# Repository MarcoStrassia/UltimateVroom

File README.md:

# UltimateVroom

UltimateVroom is a dual-motor brushless controller for a Boosted Board V1. Marco and I are building it to replace the dead stock ESC.

It runs from a 12S A123 26650 pack, which is 39.6 V nominal and 43.2 V charged, and drives two motors. An STM32F103 does the control, IRS2104 gate drivers switch CSD19532 FETs, and the board is 4 layers.

The KiCad project is in `MotorController-Rebuild/`. GitHub doesn't render KiCad files, so clone the repo and open `MotorController-Rebuild/MotorController-Rebuild.kicad_pro` in KiCad 10. `MotorController-Rebuild/docs/` has our spec PDF, design notes, and notes and photos of the stock ESC. `MotorController-Rebuild/review/current/previews/` has images of the board and a PDF of the schematic. `earlier-schematic/` is Marco's first schematic.

The board is routed. ERC has 0 errors and 7 warnings (four-way junctions). DRC has 0 errors and 0 unconnected items, and the schematic matches the board.

Still open: motor current limits, a thermal check, firmware, the Bluetooth remote, and fitting the board into the Boosted V1 ESC footprint, which is about 84 x 100 mm with six phase pads.

Patrick Liu and Marco Strassia, UCSB

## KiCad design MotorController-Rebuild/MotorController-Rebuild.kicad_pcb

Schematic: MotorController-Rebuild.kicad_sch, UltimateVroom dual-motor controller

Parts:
C1, C4: 0.1uF; C_0603_1608Metric; MPN C0603C104K5RACTU
C2, C3, C5: 0.1uF; C_0805_2012Metric; MPN C0805C104K5RACTU
C10, C15, C20, C44, C65, C70, C75, C84, C85: 1uF 50V; C_0805_2012Metric; MPN C0805C105K5RACTU
C11, C16, C21, C43, C66, C71, C76: 4.7uF 25V; C_0805_2012Metric; MPN C0805C475K3RACTU
C12, C17, C22, C31, C67, C72, C77: 2.2uF 100V; C_1210_3225Metric; MPN C1210C225K1RACTU
C14, C19, C24, C68, C73, C78: 1nF 100V C0G; C_0805_2012Metric; MPN C0805C102J1GACTU
C18, C23, C61, C64, C69, C74, C79: 100nF 50V; C_0805_2012Metric
C30, C34, C35: 100nF 50V; C_0805_2012Metric; MPN C0805C104K5RACTU
C32: 100nF 100V; C_0805_2012Metric; MPN C0805C104K1RACTU
C33: 100uF 25V; CP_Elec_8x10.5; MPN EEE-FK1E101P
C36: 4.7uF 50V; C_1206_3216Metric; MPN C1206C475K5RACTU
C37: 22uF 16V; C_1210_3225Metric; MPN C1210C226K4RACTU
C40, C41, C42, C45, C46, C47, C48, C59, C60, C81, C82, C83, C93: 100nF 50V; C_0603_1608Metric; MPN C0603C104K5RACTU
C49, C57, C80: 1nF 100V; C_0805_2012Metric
C50: 220nF 50V; C_0805_2012Metric; MPN C0805C224K5RACTU
C51, C52: 1500uF 80V; CP_Radial_D18.0mm_L35.5mm_P7.50mm_Horizontal; MPN EKYB800ELL152MMP1S
C58: 10nF 50V; C_0805_2012Metric
C62: 1uF 25V; C_0805_2012Metric
C63: 1nF 100V C0G; C_0805_2012Metric
C86, C87, C88, C89, C90, C91: 4.7nF 50V; C_0805_2012Metric; MPN C0805C472K5RACTU
C92: 10uF 10V; C_0805_2012Metric; MPN GRM21BR61A106KE19L
D1, D2, D3, D6, D7, D8: US1G-E3/61T; D_SMA; MPN US1G-E3/61T
D4: SS3H10-E3/57T; D_SMC; MPN SS3H10-E3/57T
D5: SMCJ45A-E3/57T; D_SMC; MPN SMCJ45A-E3/57T
D9: 3V3 green; LED_0805_2012Metric; MPN LTST-C171GKT
D10: 5V green; LED_0805_2012Metric; MPN LTST-C171GKT
D11: VG 12V green; LED_0805_2012Metric; MPN LTST-C171GKT
D12: RUN green; LED_0805_2012Metric; MPN LTST-C171GKT
D13: FAULT red; LED_0805_2012Metric; MPN LTST-C171KRKT
D14: BLE green; LED_0805_2012Metric; MPN LTST-C171GKT
D15: M1 ARM green; LED_0805_2012Metric; MPN LTST-C171GKT
D16: M2 ARM green; LED_0805_2012Metric; MPN LTST-C171GKT
F1: 1025HC20-RTR 20A; Fuse_1025HC; MPN 1025HC20-RTR
FB1: BLM18AG601SN1D; L_0603_1608Metric
J1: PHASE_A; SolderPad_10AWG_7x11mm_D4.0mm
J2: PHASE_B; SolderPad_10AWG_7x11mm_D4.0mm
J3: PHASE_C; SolderPad_10AWG_7x11mm_D4.0mm
J4: BOOT0 strap; PinHeader_1x02_P2.54mm_Vertical
J5: SWD target reference only; PinHeader_1x06_P2.54mm_Vertical
J6: UART 3.3V TTL; PinHeader_1x03_P2.54mm_Vertical
J7: Receiver pulse input; PinHeader_1x02_P2.54mm_Vertical
J8: NC emergency loop; PinHeader_1x02_P2.54mm_Vertical
J9: BAT+; SolderPad_10AWG_7x11mm_D4.0mm
J10: BAT-; SolderPad_10AWG_7x11mm_D4.0mm
J11: VBAT_BUS dump resistor; SolderPad_14AWG_5x8mm_D2.5mm
J12: DUMP_DRAIN dump resistor; SolderPad_14AWG_5x8mm_D2.5mm
J13: M2_PHASE_A; SolderPad_10AWG_7x11mm_D4.0mm
J14: M2_PHASE_B; SolderPad_10AWG_7x11mm_D4.0mm
J15: M2_PHASE_C; SolderPad_10AWG_7x11mm_D4.0mm
J16: HALL_M1 JST-PH 5p; JST_PH_B5B-PH-K_1x05_P2.00mm_Vertical; MPN B5B-PH-K-S(LF)(SN)
J17: HALL_M2 JST-PH 5p; JST_PH_B5B-PH-K_1x05_P2.00mm_Vertical; MPN B5B-PH-K-S(LF)(SN)
J18: BLE SWD; PinHeader_1x05_P2.54mm_Vertical; MPN PH1-05-UA (2.54 mm header)
L1: 100uH; L_Bourns_SRR1260; MPN SRR1260-101M
L2: 22uH; L_Bourns_SRN8040TA; MPN SRN8040TA-220M
MP1: MP9486GN-Z; MP9486_SOIC8_EP_0p4mm_thermal; Manufactuer PN MP9486GN-Z
Q1, Q2, Q3, Q4, Q5, Q6, Q7, Q8, Q9, Q10, Q11, Q12, Q13, Q14: CSD19532Q5B
R1, R2, R3: 10k; R_0603_1608Metric; Manufactuer PN CRT0603-BY-1002ELF
R4, R5, R88, R89: 10K; R_0603_1608Metric
R6, R7, R20, R21, R30, R31, R84, R85, R91, R92, R98, R99: 22; R_0805_2012Metric
R12, R13, R22, R23, R27, R32, R33, R37, R86, R87, R93, R94, R96, R100, R101, R103: 10k; R_0805_2012Metric
R18, R28, R38, R90, R97, R104: 10 0.5W; R_1210_3225Metric; MPN CRCW121010R0FKEA
R26, R36, R56, R57, R58, R59, R61, R63, R74, R95, R102, R108, R109, R110: 10k; R_0603_1608Metric
R50: 590k 0.1%; R_0805_2012Metric; MPN TNPW0805590KBEEA
R51, R55: 10k 0.1%; R_0805_2012Metric; MPN TNPW080510K0BEEA
R52: 69.8k 0.1%; R_0805_2012Metric; MPN TNPW080569K8BEEA
R53: 22.1k 0.1%; R_0805_2012Metric; MPN TNPW080522K1BEEA
R54: 274k 0.1%; R_0805_2012Metric; MPN TNPW0805274KBEEA
R60, R62: 1k; R_0805_2012Metric
R70, R71, R105, R106: 10m 3W; WSLP2512_10m; MPN WSLP2512R0100FEA
R72, R107: 100; R_0805_2012Metric
R73: 3.32k; R_0603_1608Metric
R75: 249k 0.1%; R_0805_2012Metric
R76, R83: 10k 0.1%; R_0603_1608Metric
R77: 4.7k; R_0603_1608Metric
R78, R80: 10; R_0805_2012Metric
R79: 100k; R_0805_2012Metric
R81: 1M 0.1%; R_0603_1608Metric
R82: 182k 0.1%; R_0805_2012Metric
R111, R112, R113, R117, R118, R119, R124: 2.2k; R_0603_1608Metric; MPN RC0603FR-072K2L
R114, R115, R116, R120, R121, R122: 10k; R_0603_1608Metric; MPN RC0603FR-0710KL
R123, R126, R127, R130: 1k; R_0603_1608Metric; MPN RC0603FR-071KL
R125: 4.7k; R_0603_1608Metric; MPN RC0603FR-074K7L
R128, R129: 1.5k; R_0603_1608Metric; MPN RC0603FR-071K5L
SW1: RESET; SW_SPST_B3U-1000P; MPN B3U-1000P
U1: STM32F103C4Tx; LQFP-48_7x7mm_P0.5mm; MPN STM32F103C4T6
U2, U3, U5, U16, U17, U18: IRS2104; SOIC-8_3.9x4.9mm_P1.27mm; MPN IRS2104STRPBF
U6: LMR51410XDBVR; SOT-23-6; MPN LMR51410XDBVR
U7: TPS3808G33DBVR; SOT-23-6; MPN TPS3808G33DBVR
U8: TPS3808G01DBVR; SOT-23-6; MPN TPS3808G01DBVR
U9, U10, U21: SN74LVC08APWR; TSSOP-14_4.4x5mm_P0.65mm; MPN SN74LVC08APWR
U11: LM74500QDDFRQ1; TI_DDF0008A; MPN LM74500QDDFRQ1
U12, U19: INA180A1IDBVR; SOT-23-5; MPN INA180A1IDBVR
U13, U14, U20: TLV1701AIDBVR; SOT-23-5; MPN TLV1701AIDBVR
U15: UCC27511ADBVR; SOT-23-6
U22: TLV76050DBZR; SOT-23-3; MPN TLV76050DBZR
U23: MDBT50Q-1MV2; Raytac_MDBT50Q; MPN MDBT50Q-1MV2
Y1: MAX7375AXR805; SOT-323_SC-70; Manufactuer PN MAX7375AXR805+T

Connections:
+3.3V: C1.1, C4.2, C37.1, C40.1, C41.1, C42.1, C43.1, C45.1, C46.1, C47.1, C48.1, C59.1, C60.1, C81.1, C82.1, C83.1, C92.1, C93.1, FB1.2, J4.1, J5.1, J8.1, J18.1, L2.2, R1.1, R52.1, R73.1, R77.1, R111.1, R112.1, R113.1, R117.1, R118.1, R119.1, R123.1, R127.1, R128.1, R129.1, U1.1 (VBAT), U1.24 (VDD), U1.36 (VDD), U1.48 (VDD), U7.3 (~MR), U7.5 (SENSE), U7.6 (VDD), U8.3 (~MR), U8.6 (VDD), U9.14 (VCC), U10.14 (VCC), U12.5 (VS), U13.5 (V+), U19.5 (VS), U20.5 (V+), U21.14 (VCC), U23.28 (VDD), U23.30 (VDDH), Y1.1 (V+)
+5V: C85.1, J16.1, J17.1, R124.1, U22.1 (OUT)
+12V: C5.2, C11.1, C16.1, C18.1, C21.1, C23.1, C33.1, C34.1, C36.1, C61.1, C62.1, C64.1, C66.1, C69.1, C71.1, C74.1, C76.1, C79.1, C84.1, D1.2 (A), D2.2 (A), D3.2 (A), D6.2 (A), D7.2 (A), D8.2 (A), L1.2, R50.1, R54.1, R125.1, U2.1 (VCC), U3.1 (VCC), U5.1 (VCC), U6.4 (EN), U6.5 (VIN), U14.5 (V+), U15.1 (V_{DD}), U16.1 (VCC), U17.1 (VCC), U18.1 (VCC), U22.2 (IN)
/BAT_FUSED: C50.2, F1.2, Q7.1 (S), Q7.2 (S), Q7.3 (S), U11.1 (EN), U11.5 (SOURCE)
/BAT_RAW: F1.1, J9.1
/BLE_NRST: J18.4, U1.41 (PB5), U23.40 (P0.18)
/BLE_STATUS: D14.1 (K), U1.3 (PC14), U23.36 (P0.14)
/BLE_UART_RX: U1.43 (PB7), U23.22 (P0.06)
/BLE_UART_TX: U1.42 (PB6), U23.24 (P0.08)
/BOOT0: J4.2, R2.1, U1.44 (BOOT0)
/BUS_ADC: C58.1, R75.2, R76.1, U1.15 (PA5)
/CURRENT_ADC: C57.1, R72.2, U1.14 (PA4)
/CURRENT_RAW: R72.1, U12.1 (OUT), U13.3 (IN-)
/DRV_A_SD: R5.2, U5.3 (~SD), U10.3 (3Y)
/DRV_B_SD: R27.1, U2.3 (~SD), U10.6 (6Y)
/DRV_C_SD: R37.1, U3.3 (~SD), U10.8 (8Y)
/DUMP_CTL: R77.2, R81.1, U14.4 (OUT), U15.6 (IN+)
/DUMP_DRAIN: J12.1, Q8.5 (D), Q8.6 (D), Q8.7 (D), Q8.8 (D)
/DUMP_GATE: Q8.4 (G), R78.2, R79.1, R80.2
/DUMP_OH: R78.1, U15.2 (OUTH)
/DUMP_OL: R80.1, U15.3 (OUTL)
/DUMP_SENSE: C63.1, R81.2, R82.2, R83.1, U14.1 (IN+)
/ENABLE_A: R57.1, U1.25 (PB12), U10.2 (2B)
/ENABLE_B: R58.1, U1.26 (PB13), U10.5 (5B)
/ENABLE_C: R59.1, U1.27 (PB14), U10.10 (10B)
/ESTOP_OK: R62.2, R63.1, U9.2 (2B)
/LED_D9_A: D9.2 (A), R123.2
/LED_D10_A: D10.2 (A), R124.2
/LED_D11_A: D11.2 (A), R125.2
/LED_D12_A: D12.2 (A), R126.2
/LED_D13_A: D13.2 (A), R127.2
/LED_FAULT: D13.1 (K), U1.2 (PC13)
/LED_M1_ARMED: D15.1 (K), U1.4 (PC15)
/LED_M2_ARMED: R3.1, R130.1, U1.20 (PB2)
/LED_RUN: R126.1, U1.28 (PB15)
/LIMIT_REF: R73.2, R74.1, U13.1 (IN+), U14.3 (IN-), U20.1 (IN+)
/M1_HALL_A: J16.2, R111.2, R114.1
/M1_HALL_A_MCU: C86.1, R114.2, U1.38 (PA15)
/M1_HALL_B: J16.3, R112.2, R115.1
/M1_HALL_B_MCU: C87.1, R115.2, U1.39 (PB3)
/M1_HALL_C: J16.4, R113.2, R116.1
/M1_HALL_C_MCU: C88.1, R116.2, U1.21 (PB10)
/M2_CURRENT_ADC: C80.1, R107.2, U1.19 (PB1)
/M2_CURRENT_RAW: R107.1, U19.1 (OUT), U20.3 (IN-)
/M2_DRV_A_SD: R89.2, U16.3 (~SD), U21.3 (3Y)
/M2_DRV_B_SD: R96.1, U17.3 (~SD), U21.6 (6Y)
/M2_DRV_C_SD: R103.1, U18.3 (~SD), U21.8 (8Y)
/M2_ENABLE_A: R108.1, U1.32 (PA11), U21.2 (2B)
/M2_ENABLE_B: R109.1, U1.33 (PA12), U21.5 (5B)
/M2_ENABLE_C: R110.1, U1.45 (PB8), U21.10 (10B)
/M2_HALL_A: J17.2, R117.2, R120.1
/M2_HALL_A_MCU: C89.1, R120.2, U1.40 (PB4)
/M2_HALL_B: J17.3, R118.2, R121.1
/M2_HALL_B_MCU: C90.1, R121.2, U1.46 (PB9)
/M2_HALL_C: J17.4, R119.2, R122.1
/M2_HALL_C_MCU: C91.1, R122.2, U1.22 (PB11)
/M2_PHASE_A: C65.2, J13.1, Q9.1 (S), Q9.2 (S), Q9.3 (S), Q10.5 (D), Q10.6 (D), Q10.7 (D), Q10.8 (D), R86.2, R90.1, U16.6 (VS)
/M2_PHASE_B: C70.2, J14.1, Q11.1 (S), Q11.2 (S), Q11.3 (S), Q12.5 (D), Q12.6 (D), Q12.7 (D), Q12.8 (D), R93.2, R97.1, U17.6 (VS)
/M2_PHASE_C: C75.2, J15.1, Q13.1 (S), Q13.2 (S), Q13.3 (S), Q14.5 (D), Q14.6 (D), Q14.7 (D), Q14.8 (D), R100.2, R104.1, U18.6 (VS)
/M2_POWER_RETURN: C66.2, C69.2, C71.2, C74.2, C76.2, C79.2, Q10.1 (S), Q10.2 (S), Q10.3 (S), Q12.1 (S), Q12.2 (S), Q12.3 (S), Q14.1 (S), Q14.2 (S), Q14.3 (S), R87.2, R94.2, R96.2, R101.2, R103.2, R105.1, R106.1, U16.4 (COM), U17.4 (COM), U18.4 (COM), U19.3 (IN+)
/M2_PWM_A: R88.1, U1.16 (PA6), U16.2 (IN)
/M2_PWM_B: R95.1, U1.17 (PA7), U17.2 (IN)
/M2_PWM_C: R102.1, U1.18 (PB0), U18.2 (IN)
/NRST: C3.1, J5.5, R1.2, SW1.1, U1.7 (NRST), U7.1 (~RESET), U8.1 (~RESET), U9.1 (1A), U13.4 (OUT), U20.4 (OUT)
/PA0_RUN: R56.1, U1.10 (PA0), U9.5 (5B)
/PHASE_A: C10.2, J1.1, Q1.1 (S), Q1.2 (S), Q1.3 (S), Q2.5 (D), Q2.6 (D), Q2.7 (D), Q2.8 (D), R12.2, R18.1, U5.6 (VS)
/PHASE_B: C15.2, J2.1, Q3.1 (S), Q3.2 (S), Q3.3 (S), Q4.5 (D), Q4.6 (D), Q4.7 (D), Q4.8 (D), R22.2, R28.1, U2.6 (VS)
/PHASE_C: C20.2, J3.1, Q5.1 (S), Q5.2 (S), Q5.3 (S), Q6.5 (D), Q6.6 (D), Q6.7 (D), Q6.8 (D), R32.2, R38.1, U3.6 (VS)
/POWER_RETURN: C11.2, C16.2, C18.2, C21.2, C23.2, C64.2, Q2.1 (S), Q2.2 (S), Q2.3 (S), Q4.1 (S), Q4.2 (S), Q4.3 (S), Q6.1 (S), Q6.2 (S), Q6.3 (S), R13.2, R23.2, R27.2, R33.2, R37.2, R70.1, R71.1, U2.4 (COM), U3.4 (COM), U5.4 (COM), U12.3 (IN+)
/PWM_A: R4.1, U1.29 (PA8), U5.2 (IN)
/PWM_B: R26.1, U1.30 (PA9), U2.2 (IN)
/PWM_C: R36.1, U1.31 (PA10), U3.2 (IN)
/RUN_OK: U9.6 (6Y), U10.1 (1A), U10.4 (4A), U10.9 (9A), U21.1 (1A), U21.4 (4A), U21.9 (9A)
/SWCLK: J5.4, U1.37 (PA14)
/SWDIO: J5.2, U1.34 (PA13)
/THROTTLE: C49.1, R60.2, R61.1, U1.11 (PA1)
/UART_RX: J6.3, U1.13 (PA3)
/UART_TX: J6.2, U1.12 (PA2)
/VBAT_BUS: C12.1, C17.1, C22.1, C31.1, C32.1, C51.1, C52.1, C67.1, C72.1, C77.1, D5.1 (A1), J11.1, MP1.3 (VIN), Q1.5 (D), Q1.6 (D), Q1.7 (D), Q1.8 (D), Q3.5 (D), Q3.6 (D), Q3.7 (D), Q3.8 (D), Q5.5 (D), Q5.6 (D), Q5.7 (D), Q5.8 (D), Q7.5 (D), Q7.6 (D), Q7.7 (D), Q7.8 (D), Q9.5 (D), Q9.6 (D), Q9.7 (D), Q9.8 (D), Q11.5 (D), Q11.6 (D), Q11.7 (D), Q11.8 (D), Q13.5 (D), Q13.6 (D), Q13.7 (D), Q13.8 (D), R75.1, R82.1
/VDDA: C2.1, C44.1, FB1.1, U1.9 (VDDA)
GND: C1.2, C2.2, C3.2, C4.1, C5.1, C12.2, C14.2, C17.2, C19.2, C22.2, C24.2, C31.2, C32.2, C33.2, C36.2, C37.2, C40.2, C41.2, C42.2, C43.2, C44.2, C45.2, C46.2, C47.2, C48.2, C49.2, C51.2, C52.2, C57.2, C58.2, C59.2, C60.2, C61.2, C62.2, C63.2, C67.2, C68.2, C72.2, C73.2, C77.2, C78.2, C80.2, C81.2, C82.2, C83.2, C84.2, C85.2, C86.2, C87.2, C88.2, C89.2, C90.2, C91.2, C92.2, C93.2, D4.2 (A), D5.2 (A2), D9.1 (K), D10.1 (K), D11.1 (K), D12.1 (K), D16.1 (K), J5.3, J5.6, J6.1, J7.2, J10.1, J16.5, J17.5, J18.5, MP1.8 (GND), MP1.9 (EP), Q8.1 (S), Q8.2 (S), Q8.3 (S), R2.2, R3.2, R4.2, R5.1, R26.2, R36.2, R51.2, R53.2, R55.2, R56.2, R57.2, R58.2, R59.2, R61.2, R63.2, R70.2, R71.2, R74.2, R76.2, R79.2, R83.2, R88.2, R89.1, R95.2, R102.2, R105.2, R106.2, R108.2, R109.2, R110.2, SW1.2, U1.8 (VSSA), U1.23 (VSS), U1.35 (VSS), U1.47 (VSS), U6.2 (GND), U7.2 (GND), U8.2 (GND), U9.7 (GND), U9.9 (9A), U9.10 (10B), U9.12 (12A), U9.13 (13B), U10.7 (GND), U10.12 (12A), U10.13 (13B), U11.2 (GND), U12.2 (GND), U12.4 (IN-), U13.2 (V-), U14.2 (V-), U15.4 (GND), U15.5 (IN-), U19.2 (GND), U19.4 (IN-), U20.2 (V-), U21.7 (GND), U21.12 (12A), U21.13 (13B), U22.3 (GND), U23.1 (GND), U23.2 (GND), U23.15 (GND), U23.33 (GND), U23.55 (GND), Y1.3 (GND)
unnamed: C14.1, R18.2
unnamed: C19.1, R28.2
unnamed: C24.1, R38.2
unnamed: C68.1, R90.2
unnamed: C73.1, R97.2
unnamed: C78.1, R104.2
unnamed: C10.1, D1.1 (K), U5.8 (VB)
unnamed: C15.1, D2.1 (K), U2.8 (VB)
unnamed: C20.1, D3.1 (K), U3.8 (VB)
unnamed: C30.2, D4.1 (K), L1.1, MP1.5 (SW)
unnamed: C65.1, D6.1 (K), U16.8 (VB)
unnamed: C70.1, D7.1 (K), U17.8 (VB)
unnamed: C75.1, D8.1 (K), U18.8 (VB)
unnamed: D14.2 (A), R128.2
unnamed: D15.2 (A), R129.2
unnamed: D16.2 (A), R130.2
unnamed: J7.1, R60.1
unnamed: J8.2, R62.1
unnamed: J18.2, U23.51 (SWDIO)
unnamed: J18.3, U23.53 (SWDCLK)
unnamed: C30.1, MP1.4 (BST)
unnamed: MP1.6 (DIM), MP1.7 (EN)
unnamed: C34.2, MP1.1 (FB), R50.2, R51.1
unnamed: Q1.4 (G), R7.2, R12.1
unnamed: Q2.4 (G), R6.2, R13.1
unnamed: Q3.4 (G), R20.2, R22.1
unnamed: Q4.4 (G), R21.2, R23.1
unnamed: Q5.4 (G), R30.2, R32.1
unnamed: Q6.4 (G), R31.2, R33.1
unnamed: Q7.4 (G), U11.6 (GATE)
unnamed: Q9.4 (G), R84.2, R86.1
unnamed: Q10.4 (G), R85.2, R87.1
unnamed: Q11.4 (G), R91.2, R93.1
unnamed: Q12.4 (G), R92.2, R94.1
unnamed: Q13.4 (G), R98.2, R100.1
unnamed: Q14.4 (G), R99.2, R101.1
unnamed: U1.5 (PD0), Y1.2 (CLOCK)
unnamed: R20.1, U2.7 (HO)
unnamed: R21.1, U2.5 (LO)
unnamed: R30.1, U3.7 (HO)
unnamed: R31.1, U3.5 (LO)
unnamed: R7.1, U5.7 (HO)
unnamed: R6.1, U5.5 (LO)
unnamed: C35.1, U6.1 (CB)
unnamed: R52.2, R53.1, U6.3 (FB)
unnamed: C35.2, L2.1, U6.6 (SW)
unnamed: R54.2, R55.1, U8.5 (SENSE)
unnamed: U9.3 (3Y), U9.4 (4A)
unnamed: C50.1, U11.4 (VCAP)
unnamed: R84.1, U16.7 (HO)
unnamed: R85.1, U16.5 (LO)
unnamed: R91.1, U17.7 (HO)
unnamed: R92.1, U17.5 (LO)
unnamed: R98.1, U18.7 (HO)
unnamed: R99.1, U18.5 (LO)

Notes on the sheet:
Control, timing, reset and boot configuration
100V MOSFETs; local SMA bootstrap diodes; prototype 20kHz PWM
12V hysteretic buck: output ESR and ripple need bench verification
Nominal 12V = 0.2V x (1 + 590k/10k)
EN/DIM linked; internal EN pull-up
3.327V nominal; 0.30A auxiliary load budget
12V supervisor threshold nominal 11.50V; open CT delay ~20ms
Receiver: 0-3.3V pulse; external power; common ground
Contact opens => stop. Firmware must require re-arm after stop.
2 x 1500 uF / 80 V lying-flat cans (3 mF); ripple rating is the limit, see BOOSTED-V1-SCHEMATIC-CHANGES.md. Precharge still required.
External dump resistor: 10ohm for now; energy, pulse duty and heatsink rating still to work out.
Dump chopper: hysteresis, stability and pulse energy still to check.
12S A123: chopper ~48V on / ~47.4V off. Still to do: U11 transient protection, precharge, feedback and cooling.
TARGET: 12S1P A123 26650 + two Boosted Board V1 motors. Exact cell revision and motor ratings still to confirm.
M2: TIM3 PA6/PA7/PB0 PWM; PB6/PB7/PB8 enables; PB1 ADC9 current. TIM1 remains motor1. No firmware yet.
Each bridge: 2 x 10mOhm parallel, gain20 => 0.100V/A; nominal trip 24.775A. Overcurrent trip threshold only, not a set motor current limit.
Single low-side shunt: synchronous sampling/reconstruction required; blind switching states and reverse/regen current not covered by INA180.
Shared 20A fuse is not an electronic battery limiter. Pack/BMS charge, discharge, cold-temperature and cell imbalance limits remain required.
9mF at43.2V stores8.398J. External precharge/contact sequencing needed. No automatic precharge on the board.
LM74500:60V recommended /65V absolute max;43.2V steady state compatible; SMCJ45A 72.7V clamp is above that limit. Keep regen off until BMS and energy handling are sorted.
R3 = PB2/BOOT1
pull-down
Raytac MDBT50Q-1MV2 (Nordic nRF52840, chip antenna), KiCad RF_Module:MDBT50Q-1MV2 / Raytac_MDBT50Q.
Supply: +3.3V into VDD and VDDH tied (datasheet 8.3: Reg0 DC/DC and LDO off below 3.6 V); DCCH and VBUS unused.
Internal 32.768 kHz RC (datasheet 8: X2 optional). UART: MCU PB6 USART1_TX(remap) -> P0.08 RXD, MCU PB7 <- P0.06 TXD.
P0.14 = BLE_STATUS (connected, active low) -> D14 and MCU PC14. MCU PB5 (open drain) -> P0.18/nRESET; J18 = SWD.
PCB: antenna end on the right board edge; datasheet 2.3 no-ground keep-out (>= 3.8 mm, every layer) under the antenna.
Primary control path (BLE remote / phone). Wired receiver J7 stays as the fallback input.
D9 3V3 OK
+3.3 V rail present
rail-driven, no MCU pin
D11 12V GATE OK
+12 V gate rail present
D10 5V HALL
+5 V hall rail present
D12 HEARTBEAT
MCU PB15, active high
blinks while firmware runs
D13 FAULT / OVER-CURRENT
MCU PC13, active LOW (sink)

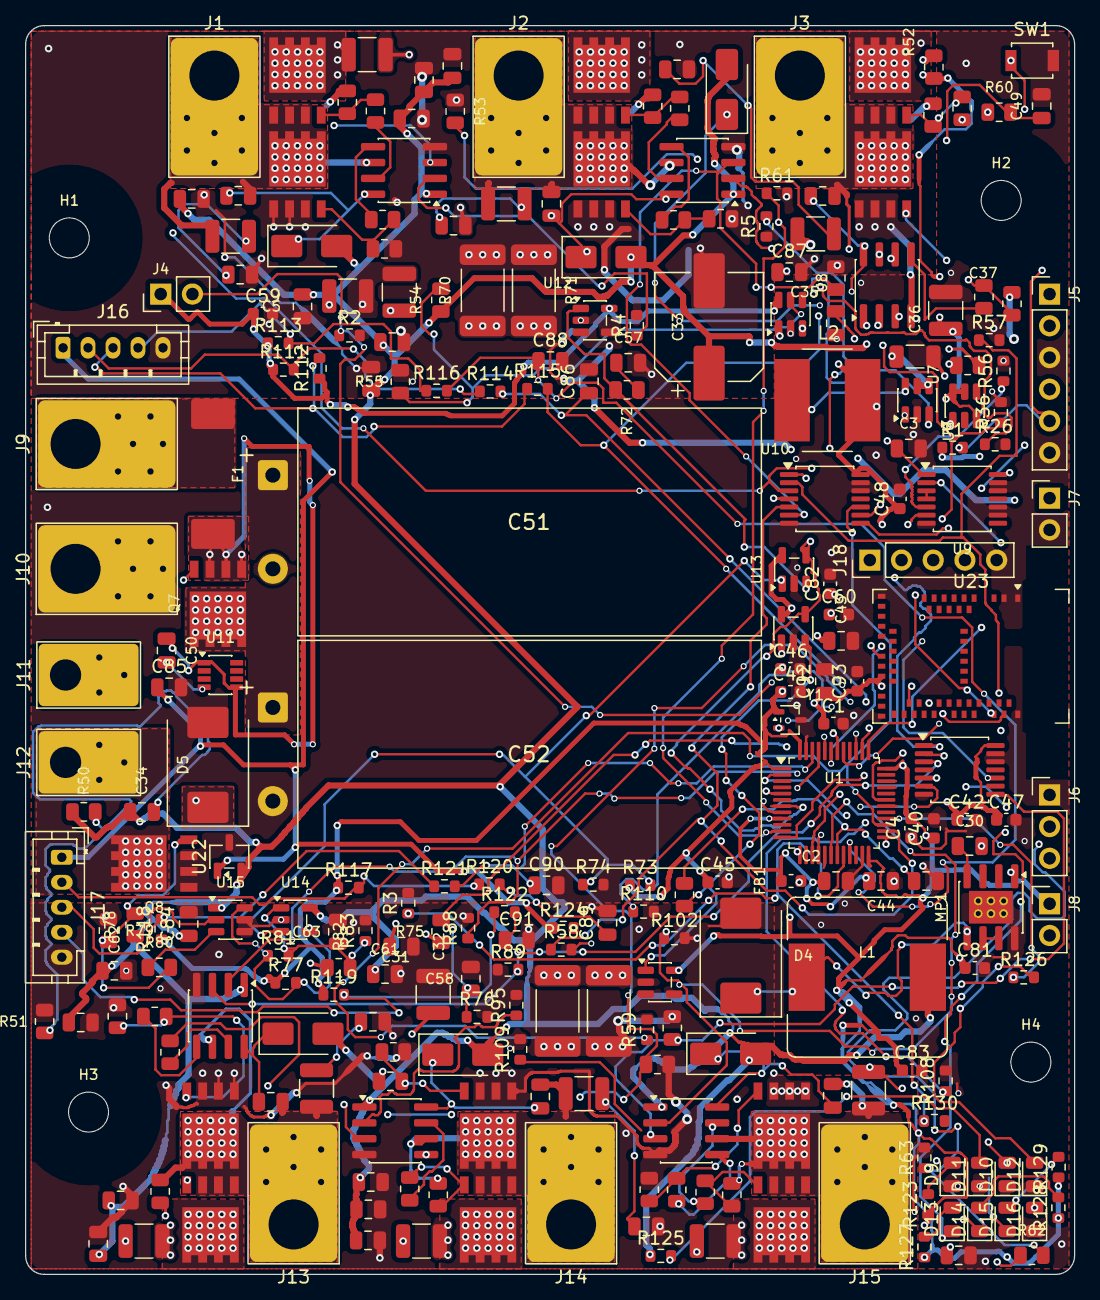
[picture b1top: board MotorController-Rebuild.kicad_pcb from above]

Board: 4 copper layers, 84.0 x 100.0 mm, 257 parts (0 on the bottom side), 136 nets.

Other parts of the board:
H1, H2, H3, H4: M3 clearance; MountingHole_3.2mm_M3
